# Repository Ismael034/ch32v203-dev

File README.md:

# ch32v203-devboard

Just another CH32V203 development board.

With dual USB, exposed GPIOs, and a SWD header, this board is meant to make it easy to create projects for the CH32V203 microcontroller.

## Screenshots

## BOM

| Qty | Designators | Description | Footprint |
| --- | --- | --- | --- |
| 2 | C1, C2 | 10 uF capacitors | `Capacitor_SMD:C_0603_1608Metric` |
| 4 | C3, C4, C9, C10 | 15 pF capacitors | `Capacitor_SMD:C_0402_1005Metric` |
| 3 | C5, C6, C7 | 100 nF capacitors | `Capacitor_SMD:C_0402_1005Metric` |
| 1 | C8 | 4.7 uF capacitor | `Capacitor_SMD:C_0402_1005Metric` |
| 1 | C11 | 10 uF capacitor | `Capacitor_SMD:C_0402_1005Metric` |
| 2 | D1, D2 | USBLC6-2P6 ESD protection | `ch32v203_dev:SOT-666-6_L1.6-W1.2-P0.50-LS1.6-BL` |
| 1 | F1 | JK-SMD0805-020-30V fuse | `Fuse:Fuse_0805_2012Metric` |
| 2 | H1, H2 | 1x20 2.54 mm pin headers | `ch32v203_dev:HDR-TH_20P-P2.54-V-M_4` |
| 1 | LED1 | User LED, XL-1608UGC-04 | `LED_SMD:LED_0603_1608Metric` |
| 1 | LDO1 | ME6211C33M5G-N 3.3 V LDO | `ch32v203_dev:SOT-23-5_L3.0-W1.7-P0.95-LS2.8-BL` |
| 1 | PWR1 | Power LED, NCD0603R1 | `LED_SMD:LED_0603_1608Metric` |
| 2 | R2, R3 | 10 kOhm resistors | `Resistor_SMD:R_0603_1608Metric` |
| 2 | R4, R5 | 1 kOhm resistors | `Resistor_SMD:R_0402_1005Metric` |
| 2 | R1, R6 | 5.1 kOhm resistors | `Resistor_SMD:R_0603_1608Metric` |
| 2 | RESET1, RESET2 | SMD tactile switches | `ch32v203_dev:SW-SMD_L3.9-W3.0-P4.45` |
| 1 | U1 | CH32V203C8U6 MCU | `ch32v203_dev:TQFN-48_L7.0-W7.0-P0.50-BL-EP5.5` |
| 1 | U2 | 2x3 2.54 mm SWD header | `ch32v203_dev:HDR-TH_6P-P2.54-V-M-R3-C2-S2.54_2` |
| 1 | U3 | 32.768 kHz crystal | `ch32v203_dev:CRYSTAL-SMD_L3.2-W1.5-1` |
| 1 | U4 | USB-C receptacle KH-TYPE-C-16P | `ch32v203_dev:USB-C-SMD_KH-TYPE-C-16P` |
| 1 | U5 | SD101CWS diode | `Diode_SMD:D_SOD-323` |
| 2 | U6, U7 | DMG2305UX-7 MOSFET | `ch32v203_dev:SOT-23-3_L2.9-W1.3-P1.90-LS2.4-BR` |
| 1 | USB2 | USB-A receptacle 10.0 QTJ6.3 | `ch32v203_dev:USB-A-SMD_10.0-QTJ6.3` |
| 1 | X1 | 8 MHz crystal | `ch32v203_dev:CRYSTAL-SMD_4P-L3.2-W2.5-BL` |

## Some notes

- You can either program the board using the USB-C port (by pressing the BOOT button while plugging in the USB cable) or using the SWD header.
- The board has a built-in LED mapped to PB9.
- The board dimensions are 27.9mm (takes 10 breadboard pins) x 59.9mm

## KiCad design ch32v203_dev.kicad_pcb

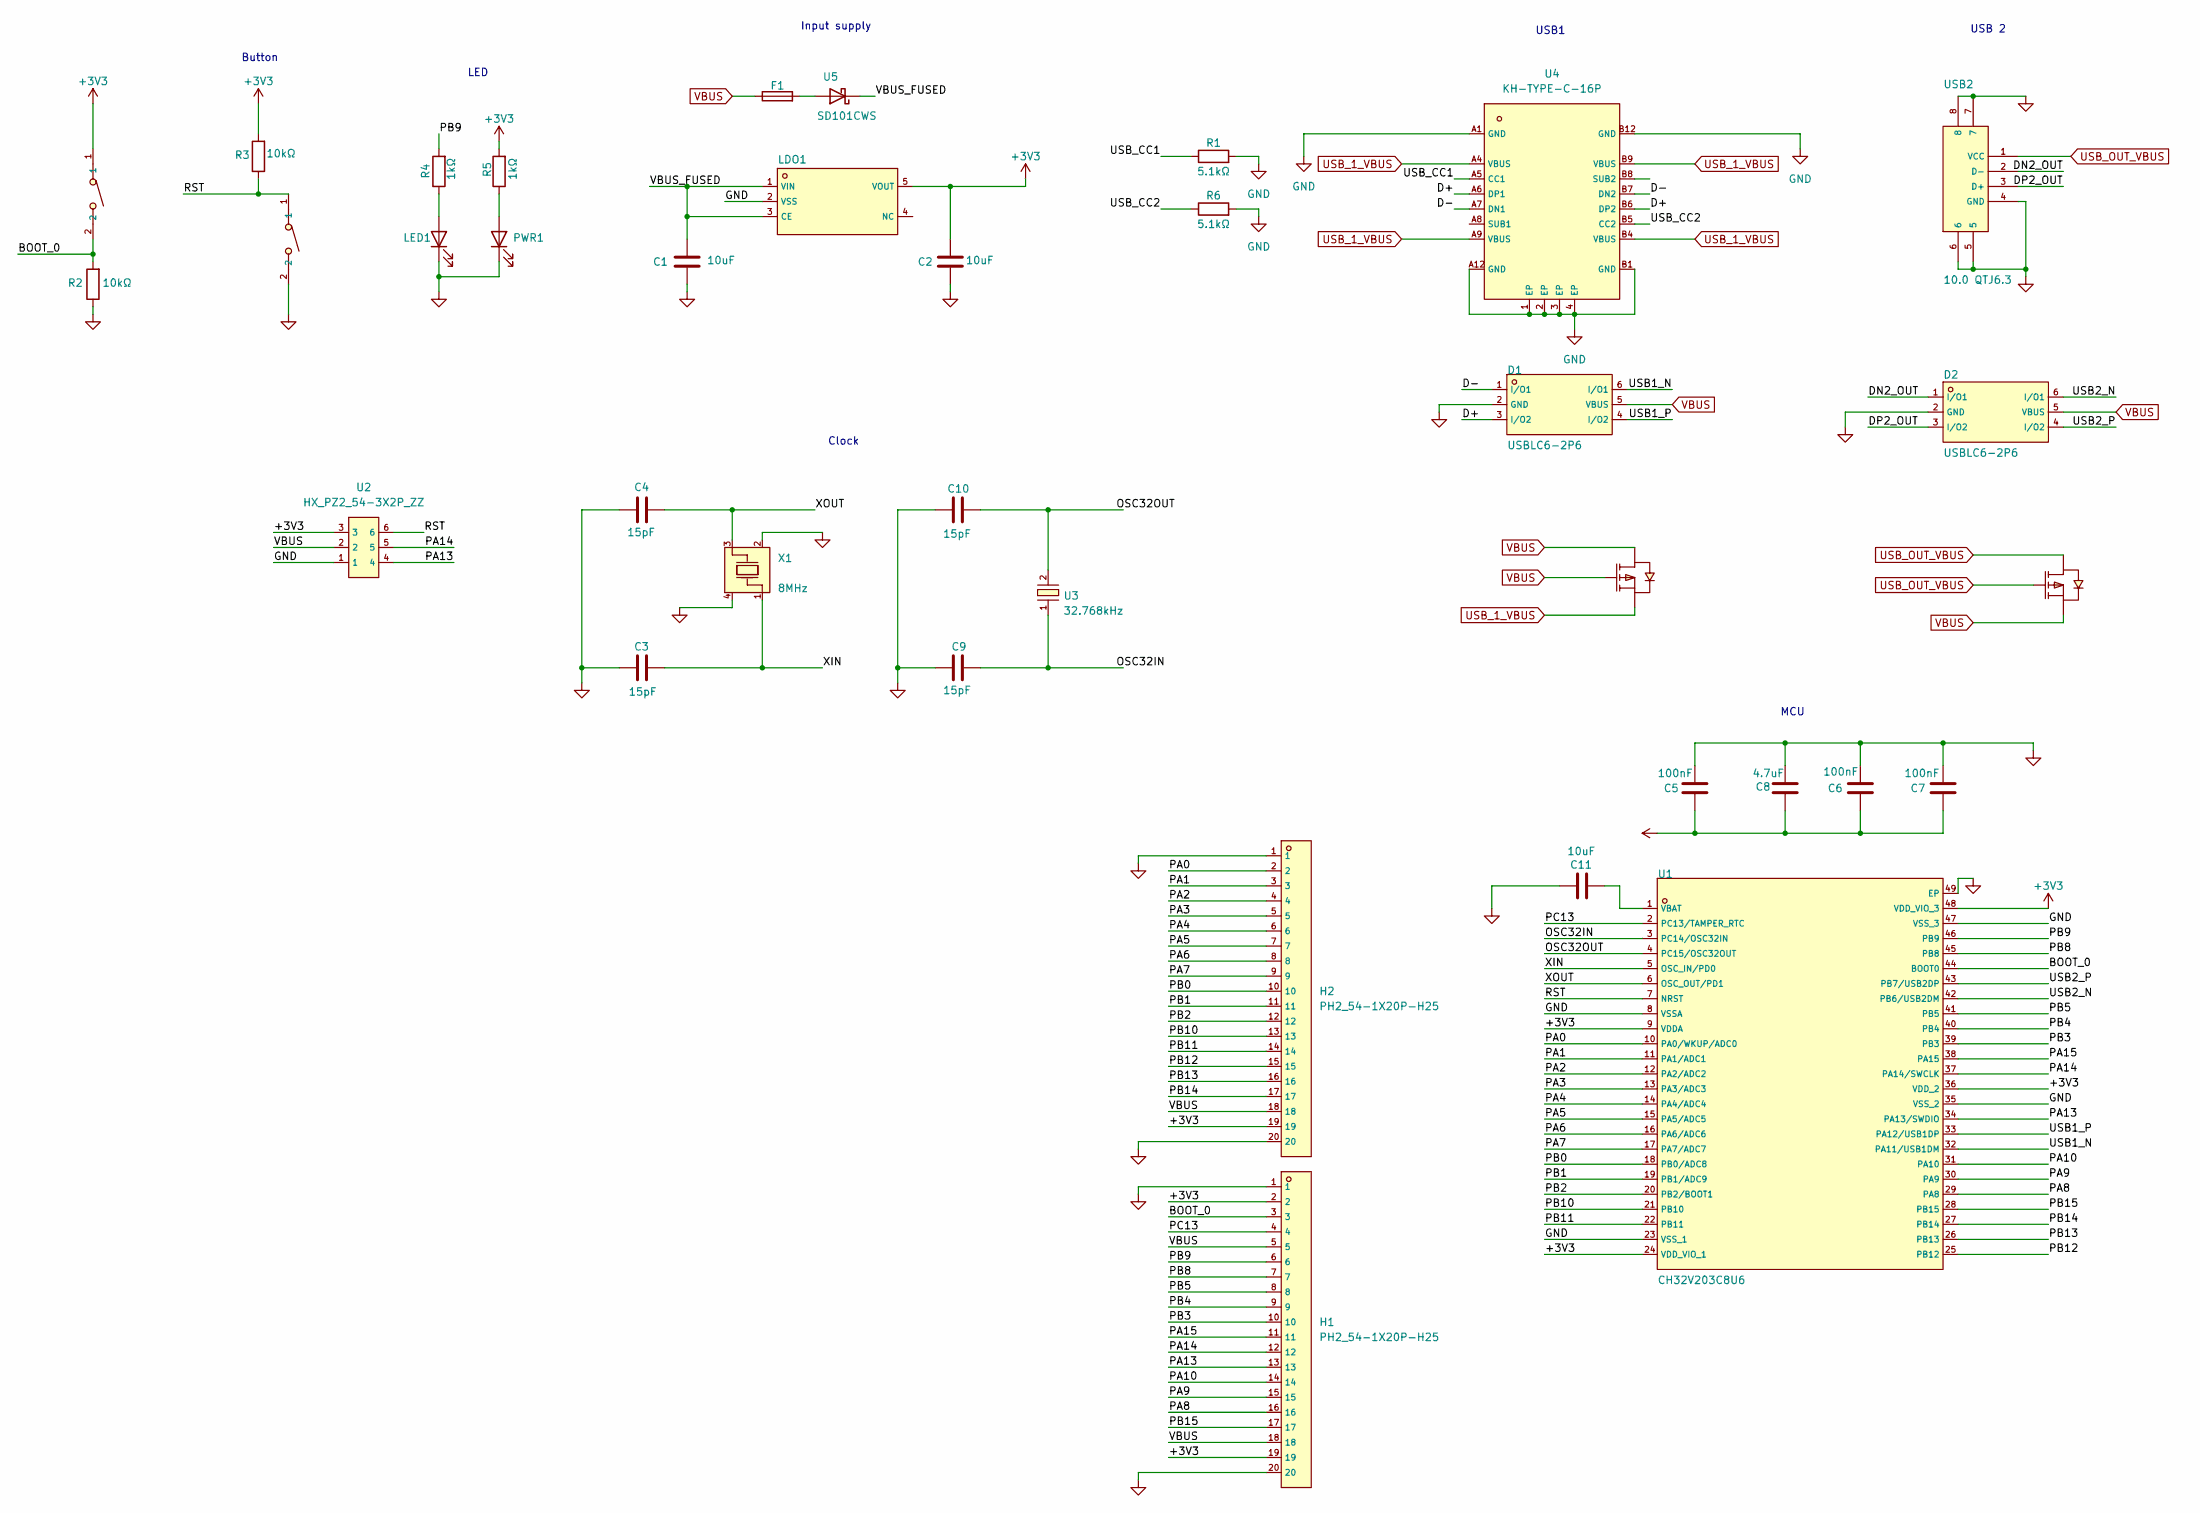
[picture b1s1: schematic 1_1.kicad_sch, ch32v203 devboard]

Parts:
C1, C2: 10uF; C_0603_1608Metric; Voltage Rating 10V; Manufacturer Part CGA0603X5R106K100JT; LCSC Part Name 10uF ±10% 10V
C3, C4, C9, C10: 15pF; C_0402_1005Metric; Manufacturer Part 0402CG150J500NT; LCSC Part Name 15pF ±5% 50V
C5, C6, C7: 100nF; C_0402_1005Metric; Manufacturer Part CGA0603X7R104K500JT; LCSC Part Name 100nF ±10% 50V
C8: 4.7uF; C_0402_1005Metric; Manufacturer Part CL10A475KP8NNNC; LCSC Part Name 4.7uF ±10% 10V
C11: 10uF; C_0402_1005Metric; Voltage Rating 10V; Manufacturer Part CGA0603X5R106K100JT; LCSC Part Name 10uF ±10% 10V
D1, D2: USBLC6-2P6; SOT-666-6_L1.6-W1.2-P0.50-LS1.6-BL; Manufacturer Part USBLC6-2P6; LCSC Part Name MSL=3
F1: JK-SMD0805-020-30V; Fuse_0805_2012Metric; Manufacturer Part JK-SMD0805-020-30V; LCSC Part Name 30V 200mA 0805自恢复
H1, H2: PH2_54-1X20P-H25; HDR-TH_20P-P2.54-V-M_4; LCSC C42431804
LDO1: ME6211C33M5G-N; SOT-23-5_L3.0-W1.7-P0.95-LS2.8-BL; Manufacturer Part ME6211C33M5G-N; LCSC Part Name 输入6V 输出3.3V 500mA
LED1: XL-1608UGC-04; LED_0603_1608Metric; Manufacturer Part XL-1608UGC-04; LCSC Part Name XL-1608UGC-04
PWR1: NCD0603R1; LED_0603_1608Metric; Manufacturer Part NCD0603R1; LCSC Part Name NCD0603R1
R1, R6: 5.1kΩ; R_0603_1608Metric
R2, R3: 10kΩ; R_0603_1608Metric; Manufacturer Part RC0603JR-0710KL; LCSC Part Name 厚膜电阻 10kΩ ±5% 100mW
R4, R5: 1kΩ; R_0402_1005Metric; Manufacturer Part 0402WGF1001TCE; LCSC Part Name 1kΩ ±1% 62.5mW 厚膜电阻
RESET1, RESET2: SW-SMD_L3.9-W3.0-P4.45; Manufacturer Part TS-1088-AR02016; LCSC Part Name 4*3*2mm 立贴 轻触开关
U1: CH32V203C8U6; TQFN-48_L7.0-W7.0-P0.50-BL-EP5.5; Manufacturer Part CH32V203C8U6; LCSC Part Name CH32V203C8U6
U2: HX_PZ2_54-3X2P_ZZ; HDR-TH_6P-P2.54-V-M-R3-C2-S2.54_2; LCSC C32713289
U3: 32.768kHz; CRYSTAL-SMD_L3.2-W1.5-1; Manufacturer Part H31003271C2070CY; LCSC Part Name 32.768kHz ±20ppm 12.5pF
U4: KH-TYPE-C-16P; USB-C-SMD_KH-TYPE-C-16P; LCSC C709357
U5: SD101CWS; D_SOD-323; Manufacturer Part SD101CWS; LCSC Part Name SD101CWS
U6, U7: DMG2305UX-7; SOT-23-3_L2.9-W1.3-P1.90-LS2.4-BR; LCSC C150470
USB2: 10.0 QTJ6.3; USB-A-SMD_10.0-QTJ6.3; Manufacturer Part 10.0 QTJ6.3; LCSC Part Name Type-A 母 卧贴
X1: 8MHz; CRYSTAL-SMD_4P-L3.2-W2.5-BL; Manufacturer Part TAXM8M4RDBCCT2T; LCSC Part Name 8MHz ±10ppm 10pF

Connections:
+3V3: C2.2, C5.1, C6.1, C7.1, C8.1, H1.2, H1.19, H2.19, LDO1.5 (VOUT), R3.2, R5.2, RESET2.1, U1.9 (VDDA), U1.24 (VDD_VIO_1), U1.36 (VDD_2), U1.48 (VDD_VIO_3), U2.3
/CH32V203/BOOT_0: H1.3, R2.2, RESET2.2, U1.44 (BOOT0)
/CH32V203/D+: D1.3 (I/O2), U4.A6 (DP1), U4.B6 (DP2)
/CH32V203/D-: D1.1 (I/O1), U4.A7 (DN1), U4.B7 (DN2)
/CH32V203/DN2_OUT: D2.1 (I/O1), USB2.2 (D-)
/CH32V203/DP2_OUT: D2.3 (I/O2), USB2.3 (D+)
/CH32V203/OSC32IN: C9.2, U1.3 (PC14/OSC32IN), U3.1
/CH32V203/OSC32OUT: C10.1, U1.4 (PC15/OSC32OUT), U3.2
/CH32V203/PA0: H2.2, U1.10 (PA0/WKUP/ADC0)
/CH32V203/PA1: H2.3, U1.11 (PA1/ADC1)
/CH32V203/PA2: H2.4, U1.12 (PA2/ADC2)
/CH32V203/PA3: H2.5, U1.13 (PA3/ADC3)
/CH32V203/PA4: H2.6, U1.14 (PA4/ADC4)
/CH32V203/PA5: H2.7, U1.15 (PA5/ADC5)
/CH32V203/PA6: H2.8, U1.16 (PA6/ADC6)
/CH32V203/PA7: H2.9, U1.17 (PA7/ADC7)
/CH32V203/PA8: H1.16, U1.29 (PA8)
/CH32V203/PA9: H1.15, U1.30 (PA9)
/CH32V203/PA10: H1.14, U1.31 (PA10)
/CH32V203/PA13: H1.13, U1.34 (PA13/SWDIO), U2.4
/CH32V203/PA14: H1.12, U1.37 (PA14/SWCLK), U2.5
/CH32V203/PA15: H1.11, U1.38 (PA15)
/CH32V203/PB0: H2.10, U1.18 (PB0/ADC8)
/CH32V203/PB1: H2.11, U1.19 (PB1/ADC9)
/CH32V203/PB2: H2.12, U1.20 (PB2/BOOT1)
/CH32V203/PB3: H1.10, U1.39 (PB3)
/CH32V203/PB4: H1.9, U1.40 (PB4)
/CH32V203/PB5: H1.8, U1.41 (PB5)
/CH32V203/PB8: H1.7, U1.45 (PB8)
/CH32V203/PB9: H1.6, R4.2, U1.46 (PB9)
/CH32V203/PB10: H2.13, U1.21 (PB10)
/CH32V203/PB11: H2.14, U1.22 (PB11)
/CH32V203/PB12: H2.15, U1.25 (PB12)
/CH32V203/PB13: H2.16, U1.26 (PB13)
/CH32V203/PB14: H2.17, U1.27 (PB14)
/CH32V203/PB15: H1.17, U1.28 (PB15)
/CH32V203/PC13: H1.4, U1.2 (PC13/TAMPER_RTC)
/CH32V203/RST: R3.1, RESET1.1, U1.7 (NRST), U2.6
/CH32V203/USB1_N: D1.6 (I/O1), U1.32 (PA11/USB1DM)
/CH32V203/USB1_P: D1.4 (I/O2), U1.33 (PA12/USB1DP)
/CH32V203/USB2_N: D2.6 (I/O1), U1.42 (PB6/USB2DM)
/CH32V203/USB2_P: D2.4 (I/O2), U1.43 (PB7/USB2DP)
/CH32V203/USB_CC1: R1.1, U4.A5 (CC1)
/CH32V203/USB_CC2: R6.1, U4.B5 (CC2)
/CH32V203/VBUS_FUSED: C1.2, LDO1.1 (VIN), LDO1.3 (CE), U5.1 (K)
/CH32V203/XIN: C3.2, U1.5 (OSC_IN/PD0), X1.1
/CH32V203/XOUT: C4.1, U1.6 (OSC_OUT/PD1), X1.3
GND: C1.1, C2.1, C3.1, C4.2, C5.2, C6.2, C7.2, C8.2, C9.1, C10.2, C11.2, D1.2 (GND), D2.2 (GND), H1.1, H1.20, H2.1, H2.20, LDO1.2 (VSS), LED1.1 (K), PWR1.1 (K), R1.2, R2.1, R6.2, RESET1.2, U1.8 (VSSA), U1.23 (VSS_1), U1.35 (VSS_2), U1.47 (VSS_3), U1.49 (EP), U2.1, U4.1 (EP), U4.2 (EP), U4.3 (EP), U4.4 (EP), U4.A1 (GND), U4.A12 (GND), U4.B1 (GND), U4.B12 (GND), USB2.4 (GND), USB2.5, USB2.6, USB2.7, USB2.8, X1.2, X1.4
unnamed: LED1.2 (A), R4.1
unnamed: PWR1.2 (A), R5.1
unnamed: C11.1, U1.1 (VBAT)
unnamed: F1.2, U5.2 (A)
USB_1_VBUS: U4.A4 (VBUS), U4.A9 (VBUS), U4.B4 (VBUS), U4.B9 (VBUS), U6.2 (S)
USB_OUT_VBUS: U7.1 (G), U7.3 (D), USB2.1 (VCC)
VBUS: D1.5 (VBUS), D2.5 (VBUS), F1.1, H1.5, H1.18, H2.18, U2.2, U6.1 (G), U6.3 (D), U7.2 (S)

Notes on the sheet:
Clock
Button
USB1
Input supply
USB 2
LED
MCU

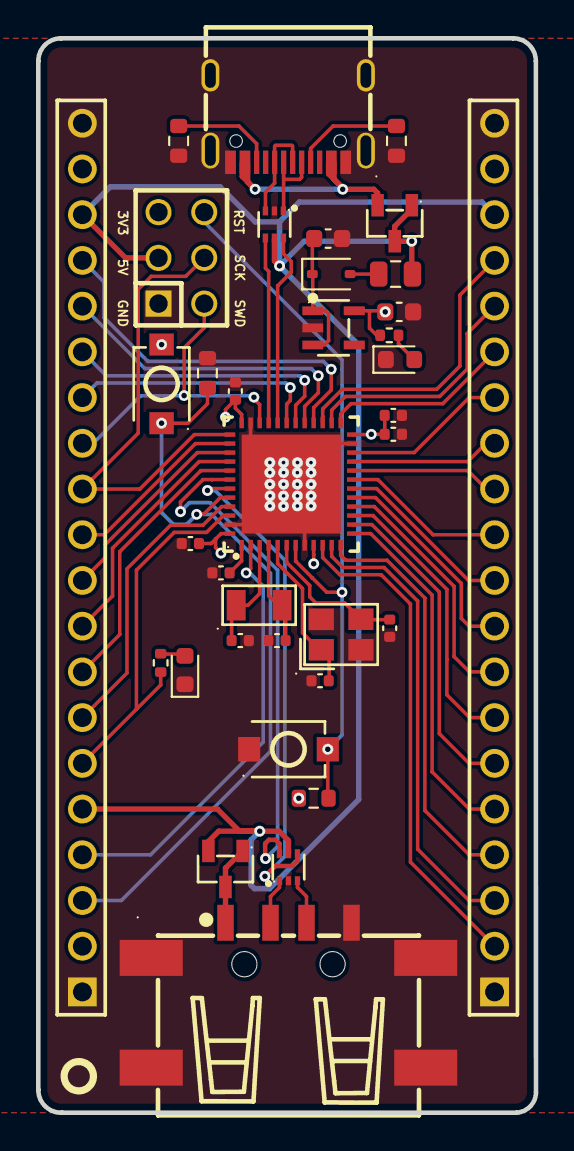
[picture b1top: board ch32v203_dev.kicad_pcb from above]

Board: 4 copper layers, 27.7 x 59.7 mm, 36 parts (0 on the bottom side), 55 nets.

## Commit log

2026-03-23 doc: add bom
2026-03-23 chore: reset components anotation
2026-03-23 chore: update schematics pdf
